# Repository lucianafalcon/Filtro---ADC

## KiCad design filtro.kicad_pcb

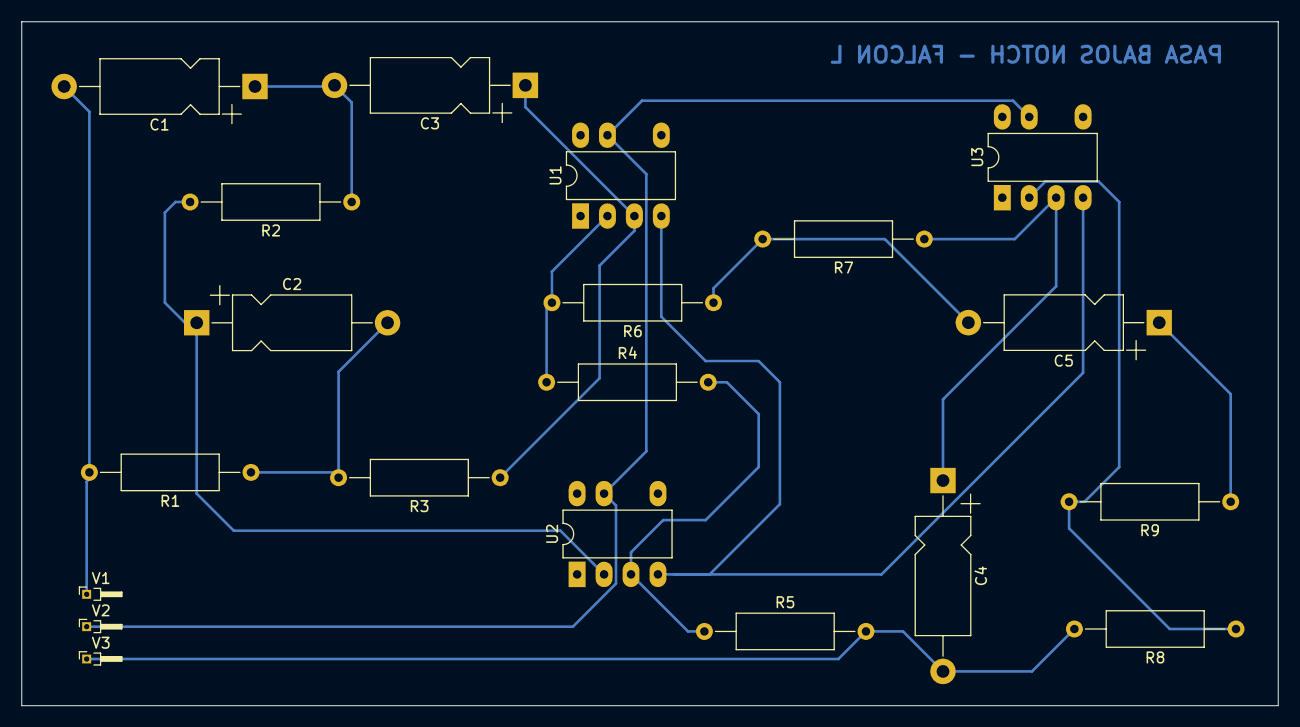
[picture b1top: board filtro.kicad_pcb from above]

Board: 2 copper layers, 118.5 x 64.5 mm, 20 parts (0 on the bottom side), 14 nets.

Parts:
C1, C3, C4, C5: 10n; CP_Axial_L11.0mm_D5.0mm_P18.00mm_Horizontal
C2: C; CP_Axial_L11.0mm_D5.0mm_P18.00mm_Horizontal
R1, R3: 200K; R_Axial_DIN0309_L9.0mm_D3.2mm_P15.24mm_Horizontal
R2: 100K; R_Axial_DIN0309_L9.0mm_D3.2mm_P15.24mm_Horizontal
R4: 6K09; R_Axial_DIN0309_L9.0mm_D3.2mm_P15.24mm_Horizontal
R5: 93K1; R_Axial_DIN0309_L9.0mm_D3.2mm_P15.24mm_Horizontal
R6, R7, R8: 13K7; R_Axial_DIN0309_L9.0mm_D3.2mm_P15.24mm_Horizontal
R9: 5K3; R_Axial_DIN0309_L9.0mm_D3.2mm_P15.24mm_Horizontal
U1, U2, U3: TL081; PowerIntegrations_PDIP-8B
V1: 1; PinHeader_1x01_P1.00mm_Horizontal
V2, V3: 5; PinHeader_1x01_P1.00mm_Horizontal

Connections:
GND: C4.2, R5.2, R8.2, V3.1 (E1)
unnamed: C1.1, C3.2, R2.1
unnamed: C1.2, R1.2, V1.1
unnamed: C2.2, R1.1, R3.2
unnamed: C5.2, R6.1, R7.2
unnamed: C3.1, R3.1, U1.3 (+)
unnamed: R4.1, R6.2, U1.2 (-)
unnamed: R4.2, R5.1, U2.3 (+)
unnamed: C2.1, R2.2, U2.2 (-)
unnamed: C4.1, R7.1, U3.3 (+)
unnamed: R8.1, R9.2, U3.2 (-)
VCC: U1.7 (V+), U2.7 (V+), U3.7 (V+), V2.1 (E1)
VEE: U1.4 (V-), U2.4 (V-), U3.4 (V-)
Vout: C5.1, R9.1

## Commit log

2025-01-25 Create Respuesta a la Cuadrada
    CODIGO MATLAB
2025-01-25 Update Respuesta a la Cuadrada
2025-01-25 Create Bode
    MATLAB
2025-01-25 Create code - Bode
    Matlab
2025-01-25 Create code - Rta a la Cuadrada
    MATLAB
2025-01-26 Create code - Rta al Impulso
    MATLAB
2025-01-26 Create code - Rta al Escalón
    MATLAB
2025-01-26 Create code - Rta al seno
    MATLAB
    rta al seno - frecuencia 500rad/seg
2025-01-26 Update code - Rta al Impulso
    MATLAB
2025-01-27 Rename Draft1.asc to ltspice.esquematico.asc
2025-01-27 Add files via upload
    PCB
